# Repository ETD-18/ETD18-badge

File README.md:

# ETD18-badge
This badge commemorates the ETD18 training group

## Schematic

## Pics

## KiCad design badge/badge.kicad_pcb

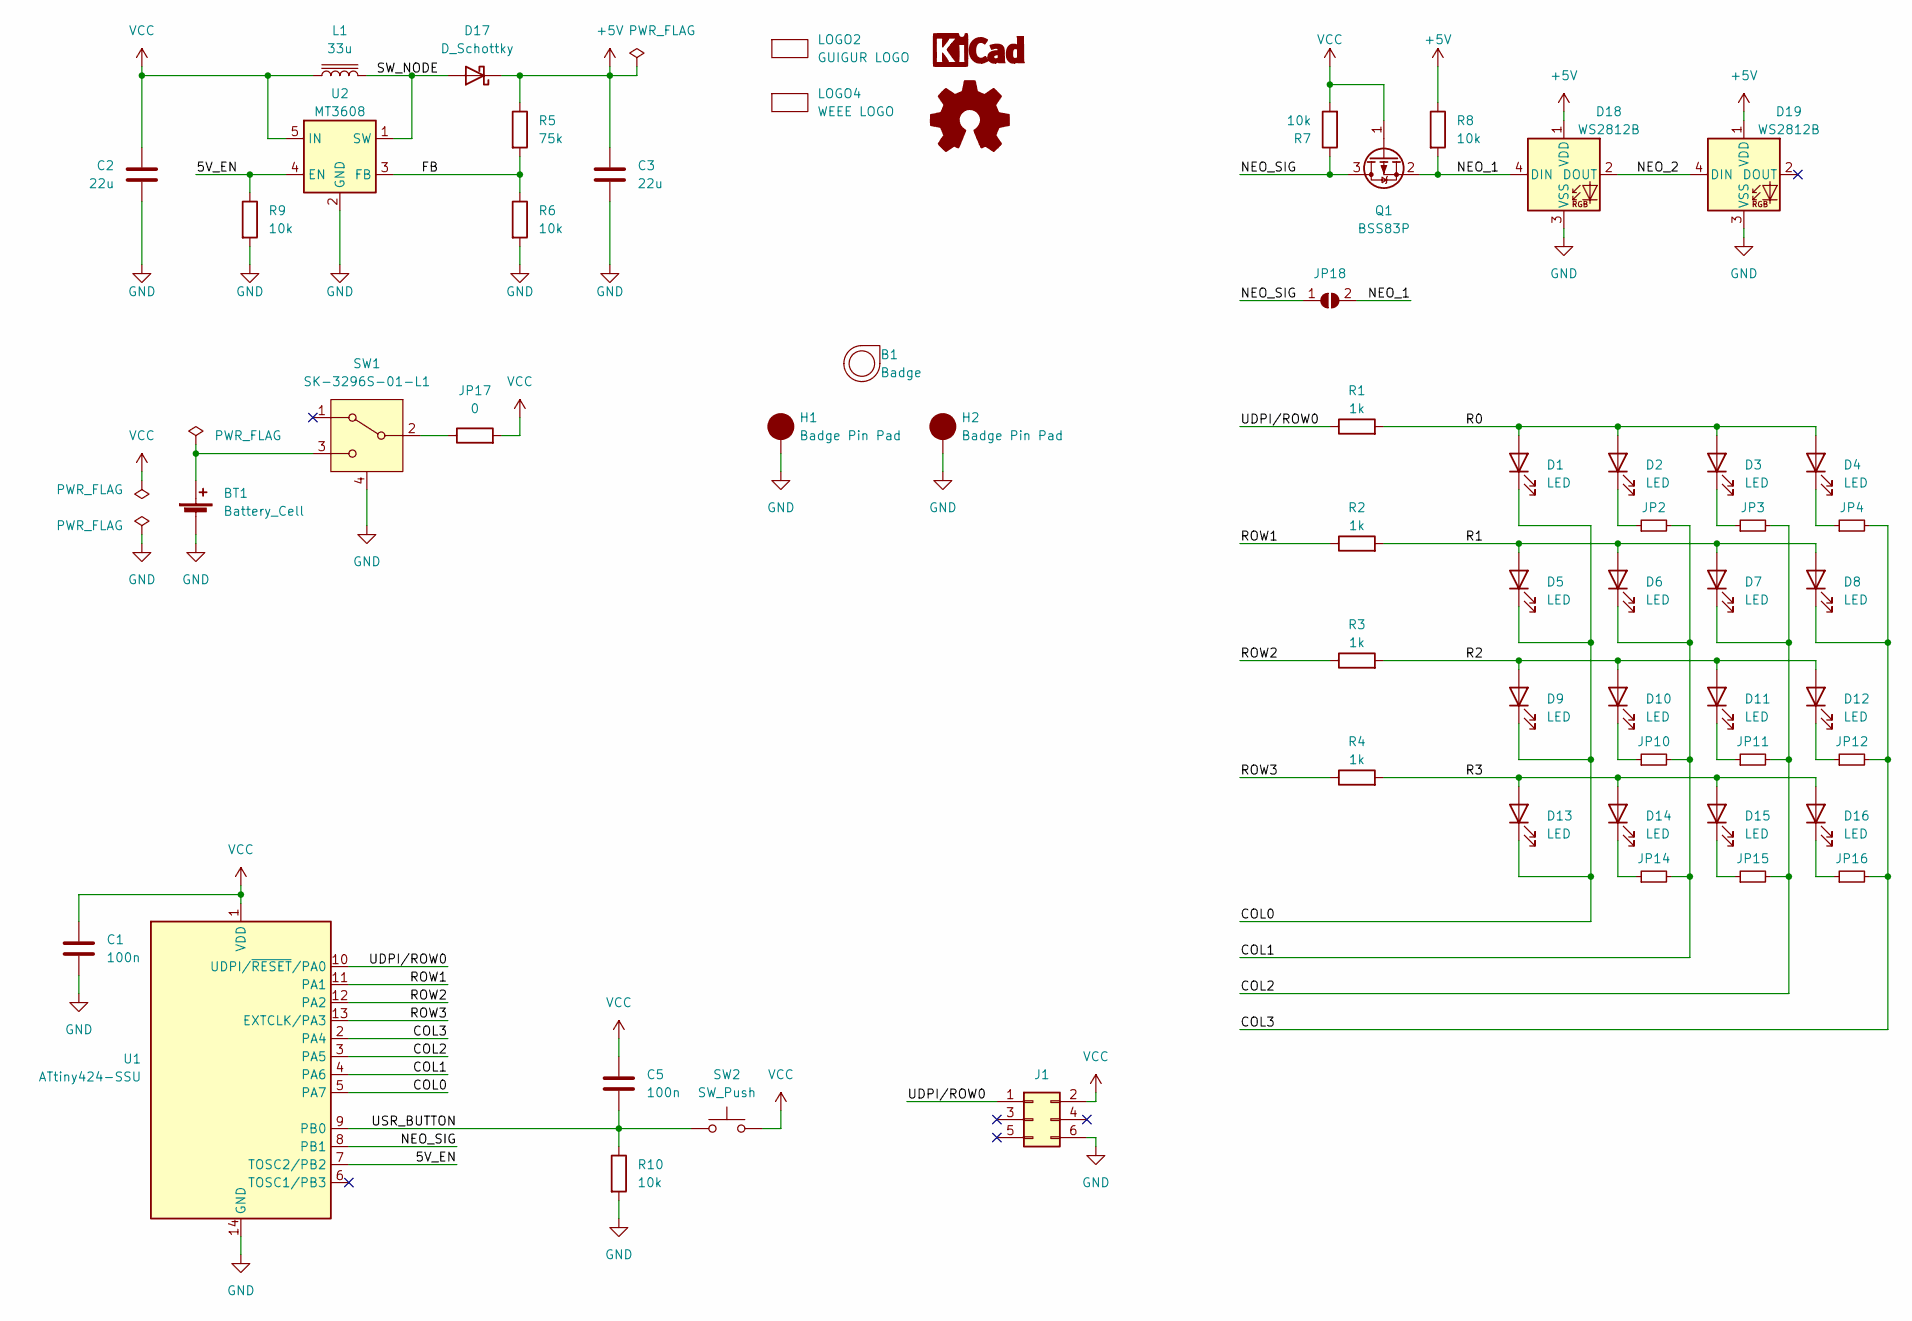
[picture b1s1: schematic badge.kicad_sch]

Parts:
B1: Badge; layers
BT1: Battery_Cell; cr_2032_holder_S8421-45R
C1, C5: 100n; C_0805_2012Metric_Pad1.18x1.45mm_HandSolder
C2, C3: 22u; R_1206_3216Metric_Pad1.30x1.75mm_HandSolder
D1, D2, D3, D4, D5, D6, D7, D8, D9, D10, D11, D12, D13, D14, D15, D16: LED; LED_0805_2012_badge
D17: D_Schottky; D_SMA
D18, D19: WS2812B; LED_WS2812B_PLCC4_5.0x5.0mm_P3.2mm
H1, H2: Badge Pin Pad; pin_badge
J1: Conn_02x03_Odd_Even; UDPI_connector
JP2, JP3, JP4, JP10, JP11, JP12, JP14, JP15, JP16: 0; R_1206_3216_jumper
JP17: 0; R_1206_3216Metric_Pad1.30x1.75mm_HandSolder
JP18: SolderJumper_2_Open; SolderJumper-2_P1.3mm_Open_TrianglePad1.0x1.5mm
L1: 33u; L_Bourns-SRN4018
LOGO1: Logo_Open_Hardware_Small; OSHW-Logo2_7.3x6mm_SilkScreen
LOGO2: GUIGUR LOGO; guigur_engineering_extra_small_logo
LOGO3: KiCAD LOGO Small; kicad_design_with_7.5mm
LOGO4: WEEE LOGO; WEEE-Logo_4.2x6mm_SilkScreen
Q1: BSS83P; SOT-23
R1, R2, R3, R4: 1k; R_1206_3216_jumper
R5: 75k; R_0603_1608Metric_Pad0.98x0.95mm_HandSolder
R6, R7, R8, R9, R10: 10k; R_0603_1608Metric_Pad0.98x0.95mm_HandSolder
SW1: SK-3296S-01-L1; sk-3296s-01-l1
SW2: SW_Push; SW_Push_1P1T_NO_6x6mm_H9.5mm
U1: ATtiny424-SSU; SOIC-14_3.9x8.7mm_P1.27mm
U2: MT3608; SOT-23-6

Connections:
+5V: C3.1, D17.1 (K), D18.1 (VDD), D19.1 (VDD), R5.1, R8.1
/5V_EN: R9.1, U1.7 (TOSC2/PB2), U2.4 (EN)
/COL0: D1.1 (K), D5.1 (K), D9.1 (K), D13.1 (K), U1.5 (PA7)
/COL1: D6.1 (K), JP2.2, JP10.2, JP14.2, U1.4 (PA6)
/COL2: D7.1 (K), JP3.2, JP11.2, JP15.2, U1.3 (PA5)
/COL3: D8.1 (K), JP4.2, JP12.2, JP16.2, U1.2 (PA4)
/FB: R5.2, R6.1, U2.3 (FB)
/NEO_1: D18.4 (DIN), JP18.2 (B), Q1.2 (S), R8.2
/NEO_2: D18.2 (DOUT), D19.4 (DIN)
/NEO_SIG: JP18.1 (A), Q1.3 (D), R7.1, U1.8 (PB1)
/R0: D1.2 (A), D2.2 (A), D3.2 (A), D4.2 (A), R1.2
/R1: D5.2 (A), D6.2 (A), D7.2 (A), D8.2 (A), R2.2
/R2: D9.2 (A), D10.2 (A), D11.2 (A), D12.2 (A), R3.2
/R3: D13.2 (A), D14.2 (A), D15.2 (A), D16.2 (A), R4.2
/ROW1: R2.1, U1.11 (PA1)
/ROW2: R3.1, U1.12 (PA2)
/ROW3: R4.1, U1.13 (EXTCLK/PA3)
/SW_NODE: D17.2 (A), L1.2, U2.1 (SW)
/UDPI/ROW0: J1.1, R1.1, U1.10 (UDPI/~RESET/PA0)
/USR_BUTTON: C5.2, R10.1, SW2.1, U1.9 (PB0)
GND: BT1.2 (-), C1.2, C2.2, C3.2, D18.3 (VSS), D19.3 (VSS), H1.1, H2.1, J1.6, R6.2, R9.2, R10.2, SW1.4 (CHASSIS), U1.14 (GND), U2.2 (GND)
unnamed: BT1.1 (+), SW1.3 (C)
unnamed: D2.1 (K), JP2.1
unnamed: D3.1 (K), JP3.1
unnamed: D4.1 (K), JP4.1
unnamed: D10.1 (K), JP10.1
unnamed: D11.1 (K), JP11.1
unnamed: D12.1 (K), JP12.1
unnamed: D14.1 (K), JP14.1
unnamed: D15.1 (K), JP15.1
unnamed: D16.1 (K), JP16.1
unnamed: JP17.1, SW1.2 (B)
VCC: C1.1, C2.1, C5.1, J1.2, JP17.2, L1.1, Q1.1 (G), R7.2, SW2.2, U1.1 (VDD), U2.5 (IN)

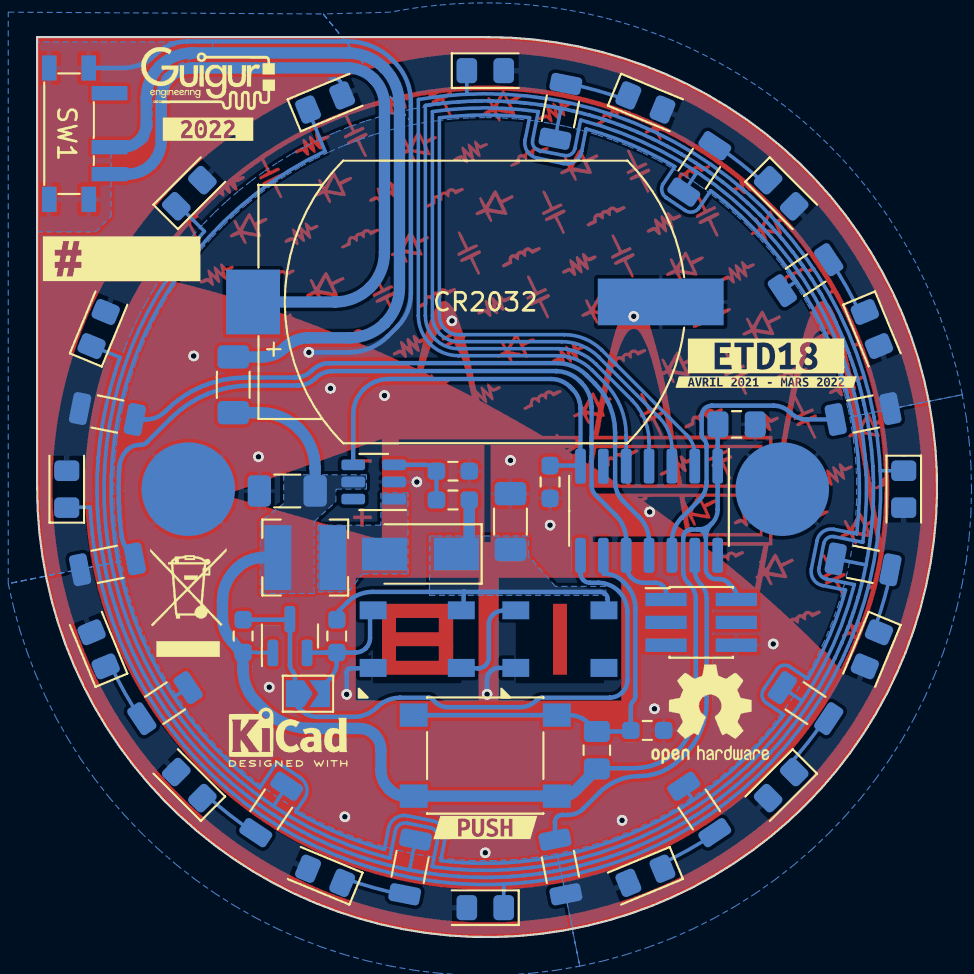
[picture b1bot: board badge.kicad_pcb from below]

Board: 2 copper layers, 50.0 x 50.0 mm, 64 parts (63 on the bottom side), 33 nets.

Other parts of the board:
kibuzzard-637A9AEB: G***; kibuzzard-637A9AEB
kibuzzard-637A9DDD: G***; kibuzzard-637A9DDD
kibuzzard-637A9580: G***; kibuzzard-637A9580
kibuzzard-637A9837: G***; kibuzzard-637A9837
kibuzzard-637A9899: G***; kibuzzard-637A9899

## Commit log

2022-06-15 stash
2022-08-07 Create main.c
    wip
2022-11-06 schematic nearlly finished + new design on inkscape
2022-11-13 wip schematic finished and slow fill on pcb. test before removing all tracks
2022-11-19 finished the led matrix
2022-11-20 routing finished. need to update one last time the badge's footprint tho
2022-11-20 updated the footprint of the badge and corrected the button footprint
2022-11-21 pcb finished and ready to be ordered
2022-11-21 added schematic
2022-11-21 small correction
2022-11-21 added gitignore
2023-01-06 debugging wip
2023-06-15 created microchip studio project
